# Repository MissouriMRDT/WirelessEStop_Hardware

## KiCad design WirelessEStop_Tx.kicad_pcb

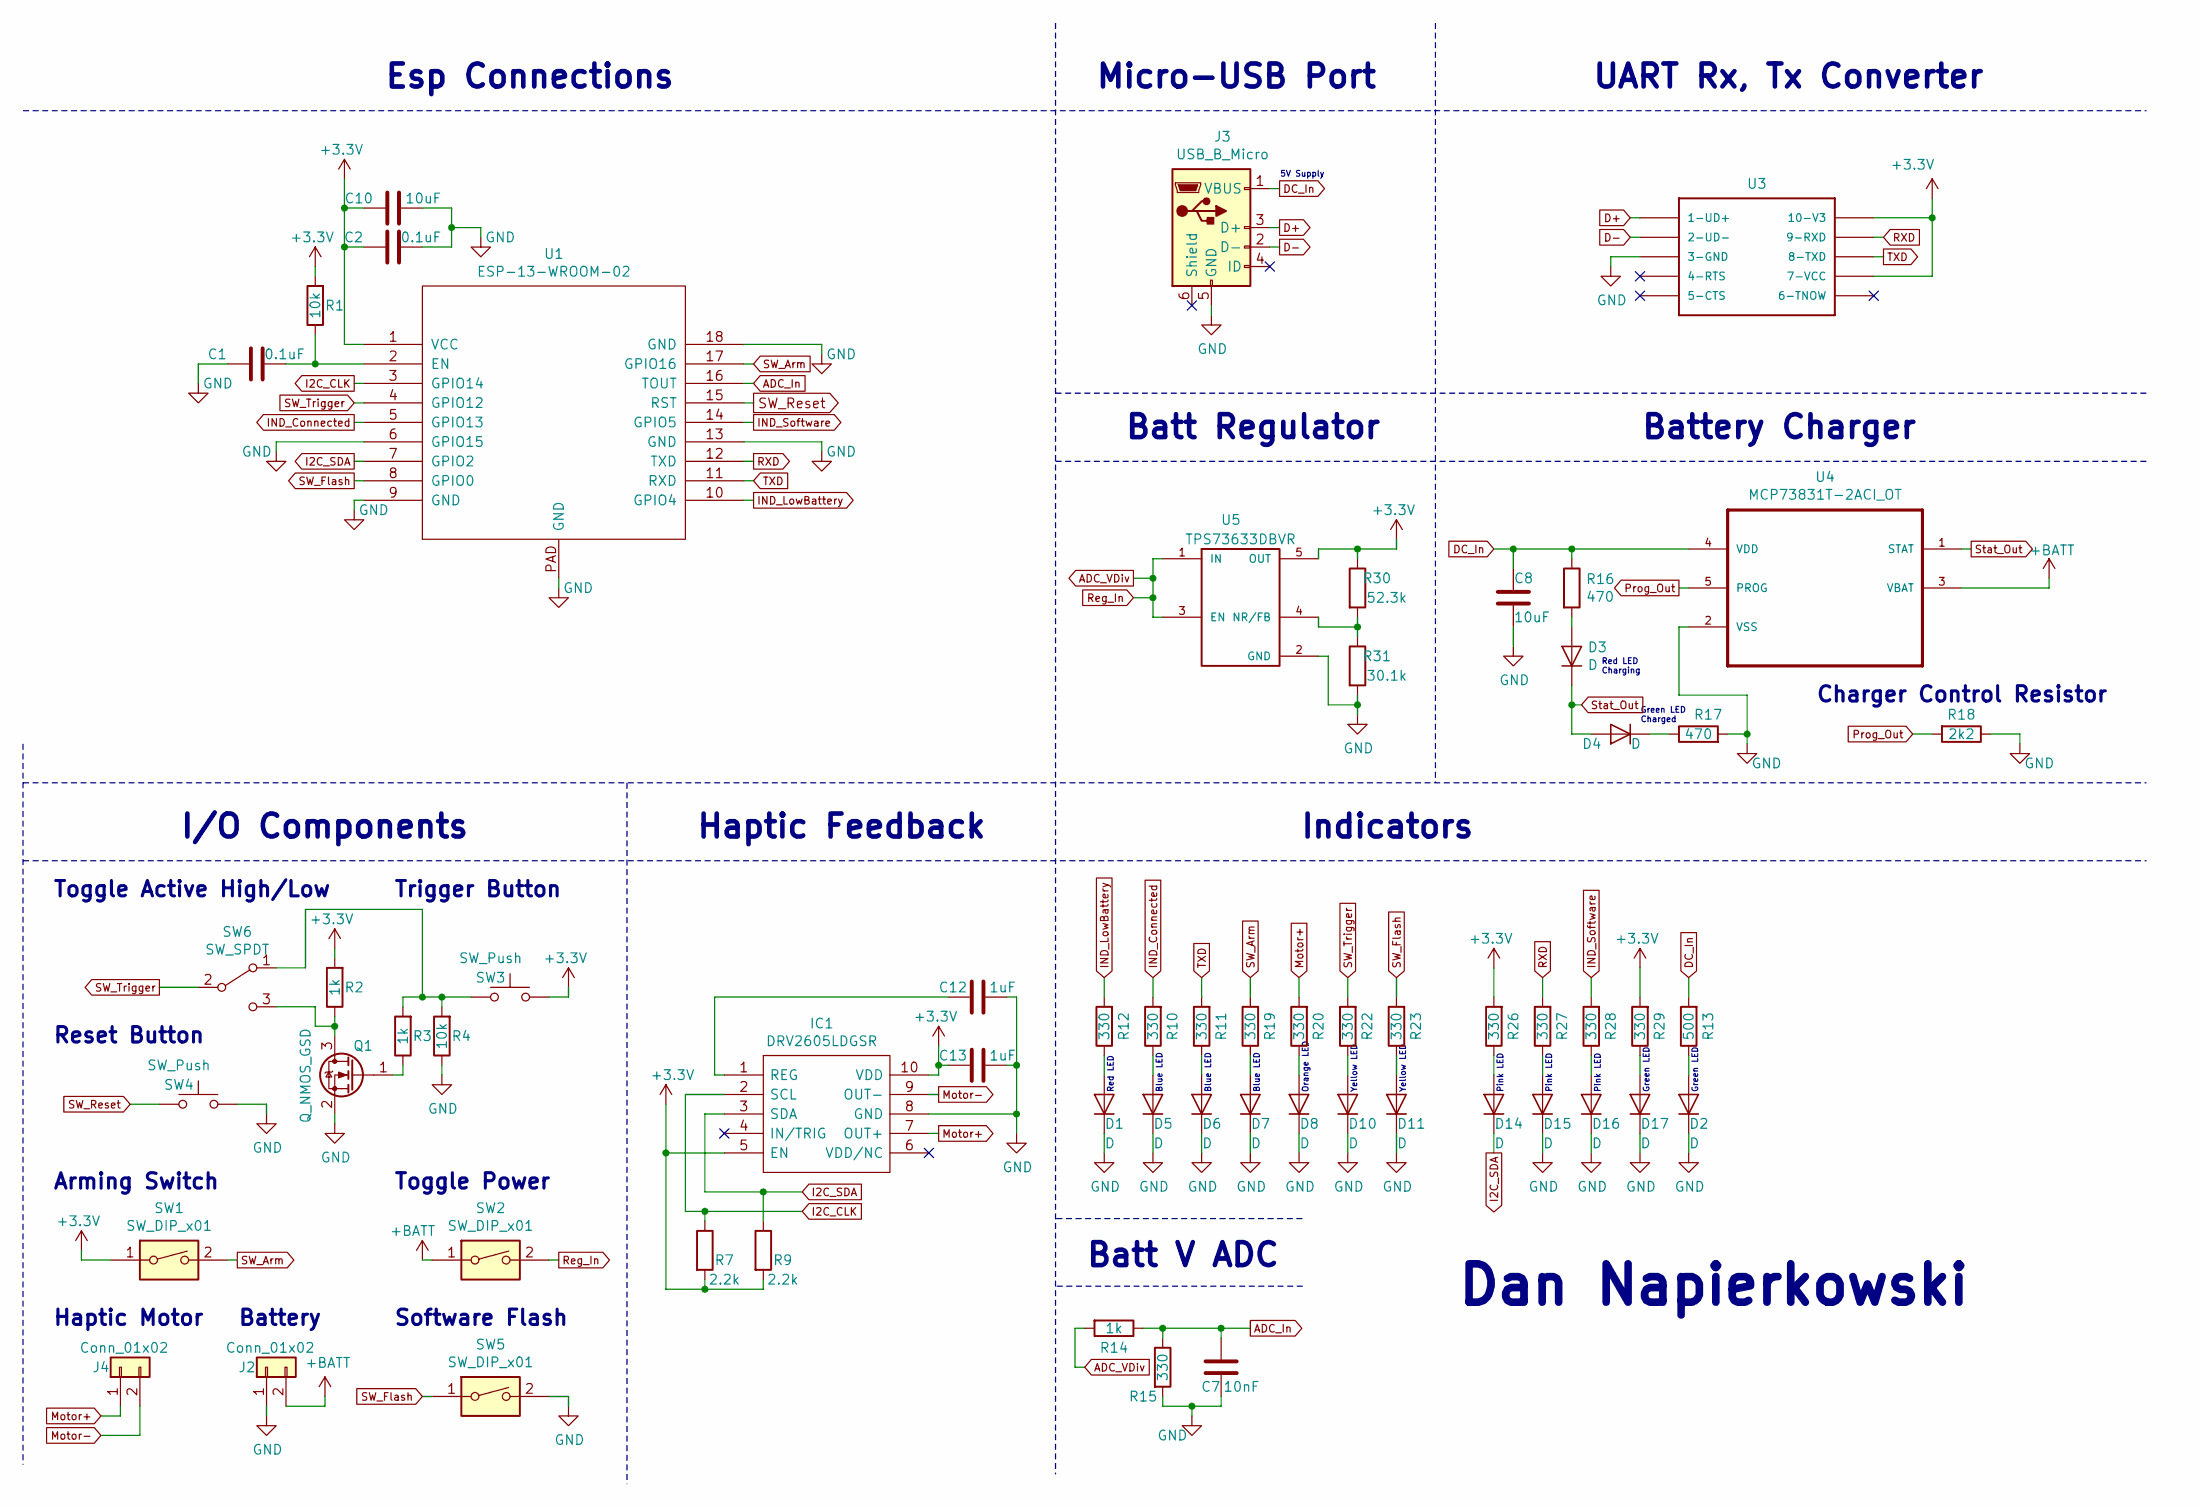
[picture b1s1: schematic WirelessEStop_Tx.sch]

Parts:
C1, C2: 0.1uF; C_0603_1608Metric_Pad1.05x0.95mm_HandSolder
C7: 10nF; C_0603_1608Metric_Pad1.05x0.95mm_HandSolder
C8, C10: 10uF; C_0603_1608Metric_Pad1.05x0.95mm_HandSolder
C12, C13: 1uF; C_0603_1608Metric_Pad1.05x0.95mm_HandSolder
D1, D2, D3, D4, D5, D6, D7, D8, D10, D11, D14, D15, D16, D17: D; LED_0603_1608Metric_Pad1.05x0.95mm_HandSolder
IC1: DRV2605LDGSR; SOP50P490X110-10N; Mouser Part Number 595-DRV2605LDGSR
J2, J4: Conn_01x02; JST_EH_B2B-EH-A_1x02_P2.50mm_Vertical
J3: USB_B_Micro; USB_Micro-B_Amphenol_10103594-0001LF_Horizontal
Q1: Q_NMOS_GSD; SOT95P240X112-3N
R1, R4: 10k; R_0603_1608Metric_Pad1.05x0.95mm_HandSolder
R2, R3, R14: 1k; R_0603_1608Metric_Pad1.05x0.95mm_HandSolder
R7, R9: 2.2k; R_0603_1608Metric_Pad1.05x0.95mm_HandSolder
R10, R11, R12, R15, R19, R20, R22, R23, R26, R27, R28, R29: 330; R_0603_1608Metric_Pad1.05x0.95mm_HandSolder
R13: 500; R_0603_1608Metric_Pad1.05x0.95mm_HandSolder
R16, R17: 470; R_0603_1608Metric_Pad1.05x0.95mm_HandSolder
R18: 2k2; R_0603_1608Metric_Pad1.05x0.95mm_HandSolder
R30: 52.3k; R_0603_1608Metric_Pad1.05x0.95mm_HandSolder
R31: 30.1k; R_0603_1608Metric_Pad1.05x0.95mm_HandSolder
SW1, SW2: SW_DIP_x01; JST_EH_B2B-EH-A_1x02_P2.50mm_Vertical
SW3: SW_Push; JST_EH_B2B-EH-A_1x02_P2.50mm_Vertical
SW4: SW_Push; SW_SPST_TL3305A
SW5: SW_DIP_x01; SW_SPST_TL3305A
SW6: SW_SPDT; JST_EH_B3B-EH-A_1x03_P2.50mm_Vertical
U1: ESP-13-WROOM-02; MODULE_ESP-WROOM-02U
U3: CH340; MSOP10
U4: MCP73831T-2ACI_OT; SOT95P280X145-5N
U5: TPS73633DBVR; SOT95P280X145-5N

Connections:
+3V3: C2.1, C10.1, C13.1, IC1.5 (EN), IC1.10 (VDD), R1.2, R2.2, R7.2, R9.2, R26.2, R29.2, R30.1, SW1.1, SW3.2, U1.1 (VCC), U3.7 (7-VCC), U3.10 (10-V3), U5.5 (OUT)
+BATT: J2.2, SW2.1, U4.3 (VBAT)
ADC_In: C7.2, R14.1, R15.1, U1.16 (TOUT)
ADC_VDiv: R14.2, SW2.2, U5.1 (IN), U5.3 (EN)
D+: J3.3 (D+), U3.1 (1-UD+)
D-: J3.2 (D-), U3.2 (2-UD-)
DC_In: C8.1, J3.1 (VBUS), R13.2, R16.1, U4.4 (VDD)
I2C_CLK: IC1.2 (SCL), R7.1, U1.3 (GPIO14)
I2C_SDA: D14.1 (K), IC1.3 (SDA), R9.1, U1.7 (GPIO2)
IND_Connected: R10.2, U1.5 (GPIO13)
IND_LowBattery: R12.2, U1.10 (GPIO4)
IND_Software: R28.2, U1.14 (GPIO5)
Motor+: IC1.7 (OUT+), J4.1, R20.2
Motor-: IC1.9 (OUT-), J4.2
unnamed: C1.2, R1.1, U1.2 (EN)
unnamed: C12.1, IC1.1 (REG)
unnamed: D1.2 (A), R12.1
unnamed: D2.2 (A), R13.1
unnamed: D3.2 (A), R16.2
unnamed: D4.1 (K), R17.1
unnamed: D5.2 (A), R10.1
unnamed: D6.2 (A), R11.1
unnamed: D7.2 (A), R19.1
unnamed: D8.2 (A), R20.1
unnamed: D10.2 (A), R22.1
unnamed: D11.2 (A), R23.1
unnamed: D14.2 (A), R26.1
unnamed: D15.2 (A), R27.1
unnamed: D16.2 (A), R28.1
unnamed: D17.2 (A), R29.1
unnamed: Q1.1 (G), R3.1
unnamed: Q1.3 (D), R2.1, SW6.3 (C)
unnamed: R3.2, R4.2, SW3.1, SW6.1 (A)
unnamed: R30.2, R31.1, U5.4 (NR/FB)
Prog_Out: R18.2, U4.5 (PROG)
RXD: R27.2, U1.12 (TXD), U3.9 (9-RXD)
SW_Arm: R19.2, SW1.2, U1.17 (GPIO16)
SW_Flash: R23.2, SW5.1, U1.8 (GPIO0)
SW_Reset: SW4.1, U1.15 (RST)
SW_Trigger: R22.2, SW6.2 (B), U1.4 (GPIO12)
Stat_Out: D3.1 (K), D4.2 (A), U4.1 (STAT)
TXD: R11.2, U1.11 (RXD), U3.8 (8-TXD)

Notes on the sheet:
Esp Connections
Micro-USB Port
Battery Charger
Indicators
Charger Control Resistor
Toggle Active High/Low
Trigger Button
Red LED Charging
Green LED Charged
Reset Button
Batt V ADC
5V Supply
I/O Components
Batt Regulator
Haptic Feedback
Haptic Motor
Software Flash
Battery
Toggle Power
Arming Switch
Yellow LED
Blue LED
Orange LED
Pink LED
Green LED
Red LED
Dan Napierkowski
UART Rx, Tx Converter

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
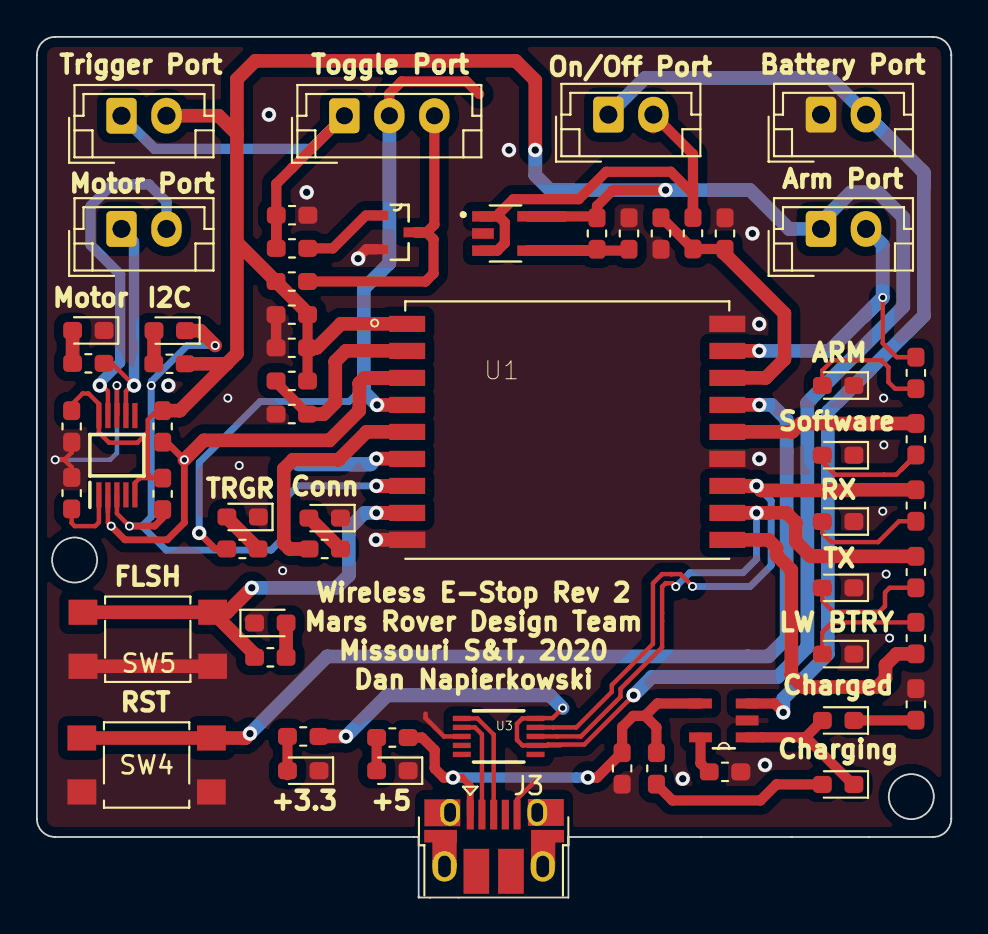
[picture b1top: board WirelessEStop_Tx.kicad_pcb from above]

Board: 2 copper layers, 50.8 x 47.8 mm, 62 parts (1 on the bottom side), 44 nets.

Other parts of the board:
R5: 0; R_0603_1608Metric_Pad1.05x0.95mm_HandSolder

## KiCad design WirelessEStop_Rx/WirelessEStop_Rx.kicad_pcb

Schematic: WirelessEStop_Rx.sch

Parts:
C1, C2: 10u; C_0603_1608Metric_Pad1.05x0.95mm_HandSolder
Conn1: E-Stop_to_BMS; MOLEX_SL_02_Horizontal_NoHole
Conn2: 9V Battery; MOLEX_SL_02_Horizontal_NoHole
D1, D2, D3: LED; LED_0603_1608Metric_Pad1.05x0.95mm_HandSolder
PWR_SW1: SW_Push_SPDT; SW_CuK_OS102011MA1QN1_SPDT_Angled
Q1: 2N7002; SOT-23
R1, R2, R3: 500; R_0603_1608Metric_Pad1.05x0.95mm_HandSolder
U1: OKI; OKI_Horizontal
U2: ESP_8266_01; ESP8266-01

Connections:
+3V3: C2.1, D3.2, U1.3, U2.8
GND: C1.2, C2.2, Conn2.1, R1.2, R2.2, R3.2, U1.2, U2.1
unnamed 2: C1.1, U1.1; also elsewhere on the board
unnamed: Conn1.1, Q1.3 (D)
unnamed: Conn1.2, Q1.2 (S)
unnamed 5: Conn2.2; also elsewhere on the board
unnamed: D1.1, R1.1
unnamed: D1.2, Q1.1 (G), U2.5
unnamed: D2.1, R2.1
unnamed: D2.2, U2.3
unnamed: D3.1, R3.1

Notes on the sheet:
Blue
Red
Green
POWER INPUT
ESP-01 & E-Stop Circuit

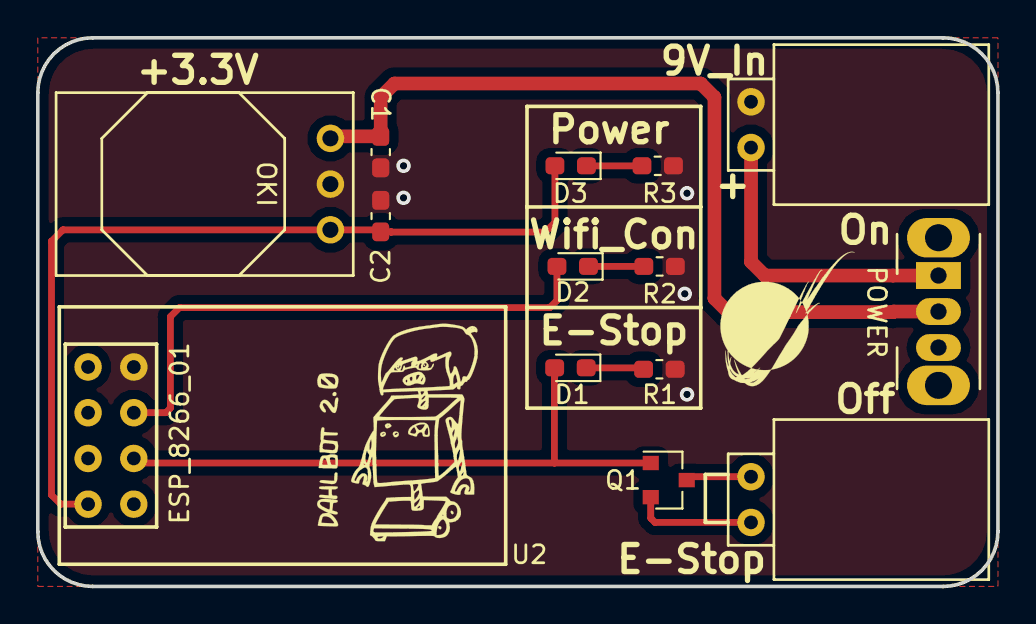
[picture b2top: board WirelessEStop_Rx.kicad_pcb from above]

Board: 2 copper layers, 53.3 x 30.5 mm, 14 parts (0 on the bottom side), 11 nets.

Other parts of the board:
POWER: SW_Push_SPDT; SW_CuK_OS102011MA1QN1_SPDT_Angled

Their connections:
unnamed 2: POWER.2; also elsewhere on the board
unnamed 5: POWER.1; also elsewhere on the board

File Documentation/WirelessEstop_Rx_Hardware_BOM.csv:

Id,Designator,Package,Designation,,Item Name,Part Number,,,Vendor,Quantity,Cost Per Item,,Cost,URL,Comments
,PWR_SW1,SW_CuK_OS102011MA1QN1_SPDT_Angled,Power Switch,,SWITCH SLIDE SPDT 100MA 12V ,CKN9565-ND,,,Digikey,1,"$0.45 for 1, $4.38 for 10",,,https://www.digikey.com/product-detail/en/c-k/OS102011MS2QN1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,
,"C1,C2",C_0603_1608Metric_Pad1.05x0.95mm_HandSolder,10u,,Capacitor,1276-1119-1-ND,,,Digikey,2,"$0.18 for 1, $1.32 for 10",,,https://www.digikey.com/product-detail/en/samsung-electro-me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,
,D1,LED_0603_1608Metric_Pad1.05x0.95mm_HandSolder,LED,,LED RED CLEAR CHIP SMD,160-1447-1-ND,,,Digikey,1,"$0.29 for 1, $2.15 for 10",,,https://www.digikey.com/product-detail/en/lite-on-inc/LTST-C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,
,D2,LED_0603_1608Metric_Pad1.05x0.95mm_HandSolder,LED,,LED BLUE CLEAR CHIP SMD,160-1647-1-ND,,,Digikey,1,"$0.53 for 1, $3.84 for 10",,,https://www.digikey.com/product-detail/en/lite-on-inc/LTST-C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,
,D3,LED_0603_1608Metric_Pad1.05x0.95mm_HandSolder,LED,,LED GREEN CLEAR CHIP SMD,160-1446-1-ND,,,Digikey,1,"$0.29 for 1, $2.15 for 10",,,https://www.digikey.com/product-detail/en/lite-on-inc/LTST-C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,
,Q1,SOT-23,2N7002,,MOSFET N-CH 60V 115MA SOT-23 ,2N7002NCT-ND,,,Digikey,1,"$0.39 for 1, $3.61 for 10",,,https://www.digikey.com/product-detail/en/on-semiconductor/2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,
,"R1,R2,R3",R_0603_1608Metric_Pad1.05x0.95mm_HandSolder,500,,Resistor,RHM510DCT-ND,,,Digikey,3,"$0.10 for 1, $0.87 for 10",,,https://www.digikey.com/product-detail/en/rohm-semiconductor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,
,U1,OKI_Horizontal,OKI,,OKI,811-3014-ND,,,Digikey,1,$4.54 for 1,,,https://www.digikey.com/product-detail/en/murata-power-solut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,
,U2,ESP8266-01,ESP_8266_01,,ESP8266-01,1568-1235-ND,,,Digikey,1,$6.95 for 1,,,https://www.digikey.com/product-detail/en/sparkfun-electroni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,
,Conn1,MOLEX_SL_02_Horizontal_NoHole,E-Stop_to_BMS,,Connector,WM4900-ND,,,Digikey,1,$0.71 for 1,,,https://www.digikey.com/products/en?keywords=WM4900-ND,
,Conn2,MOLEX_SL_02_Horizontal_NoHole,9V Battery,,Connector,WM4900-ND,,,Digikey,1,$0.71 for 1,,,https://www.digikey.com/products/en?keywords=WM4900-ND,

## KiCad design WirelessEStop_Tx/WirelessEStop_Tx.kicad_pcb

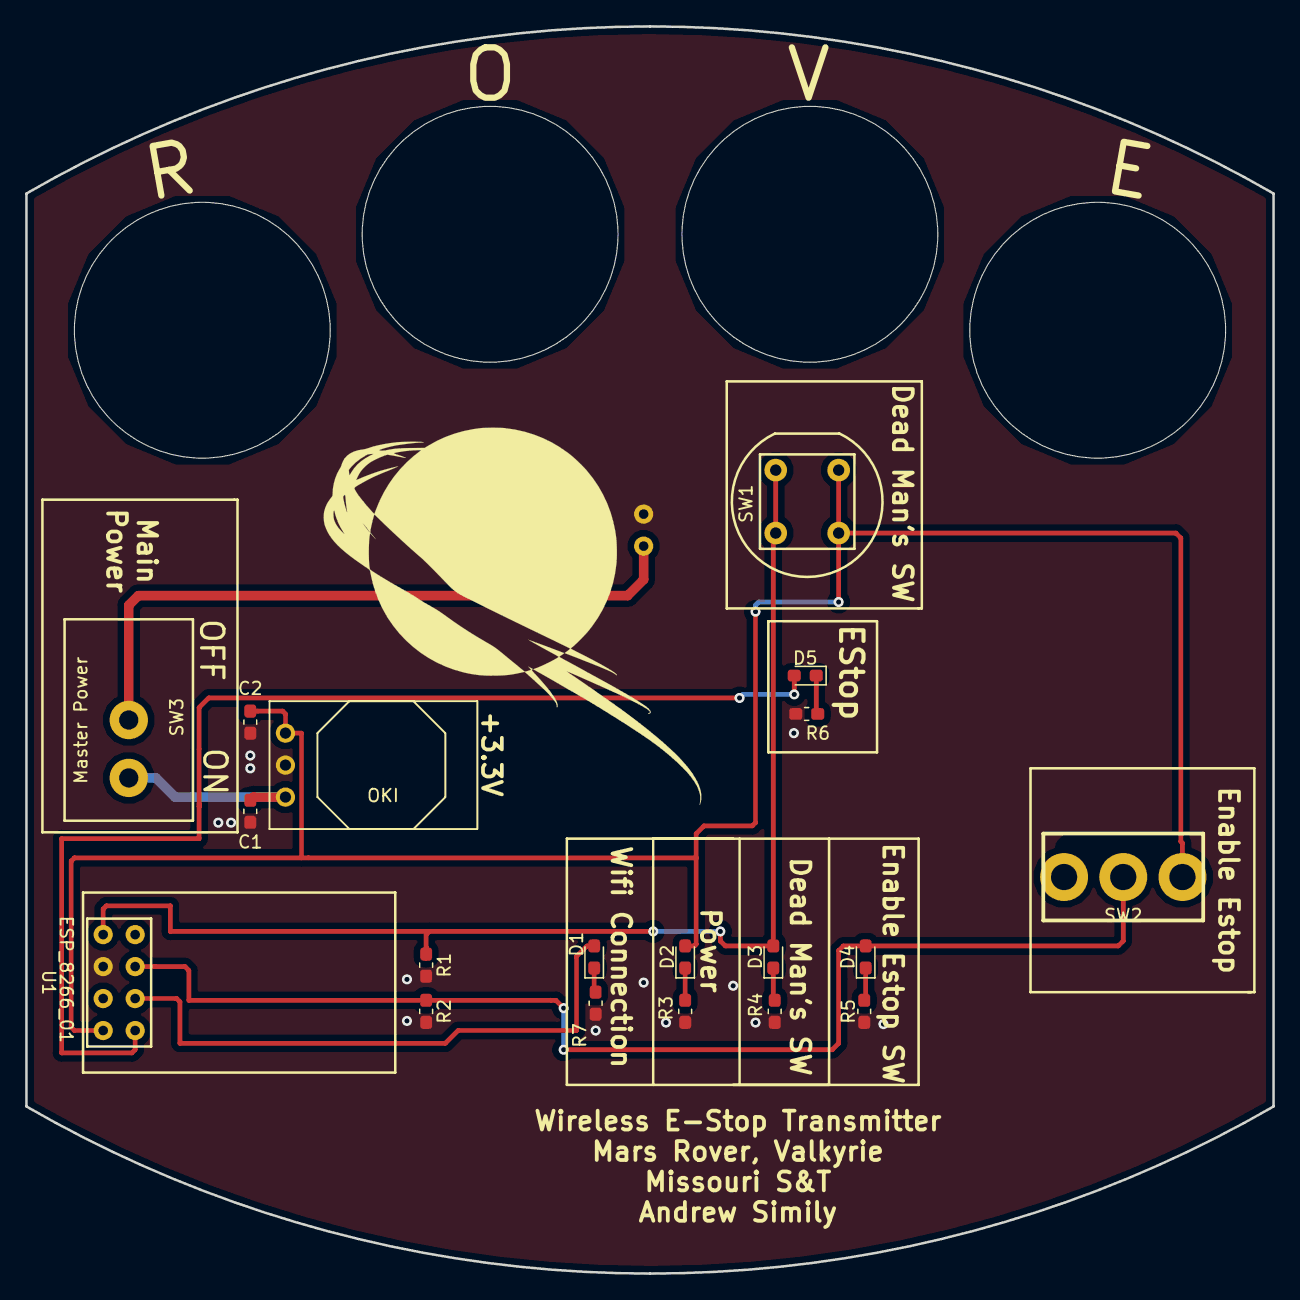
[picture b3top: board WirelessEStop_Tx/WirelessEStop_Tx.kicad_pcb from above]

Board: 2 copper layers, 99.1 x 99.1 mm, 20 parts (1 on the bottom side), 13 nets.

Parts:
C1, C2: 10u; C_0603_1608Metric_Pad1.05x0.95mm_HandSolder
Conn1: 9V Batt; MOLEX_SL_02_Horizontal_NoHole
D1, D2, D3, D4, D5: LED; LED_0603_1608Metric_Pad1.05x0.95mm_HandSolder
R1, R2: 10K; R_0603_1608Metric_Pad1.05x0.95mm_HandSolder
R3, R4, R5, R6, R7: 500; R_0603_1608Metric_Pad1.05x0.95mm_HandSolder
SW1: MOM Switch; D6_SPST
SW2: Maintain Switch; ToggleSwitch_SPDT
SW3: Master Power; SlideSwitch_SPST
U1: ESP_8266_01; ESP8266-01
U2: OKI; OKI_Horizontal

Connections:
+3V3: C2.2, D2.2, SW1.1, SW2.3, U1.8, U2.3
/Vin: Conn1.2, SW3.2
GND: C1.1, C2.1, Conn1.1, R1.2, R2.2, R3.2, R4.2, R5.2, R6.2, R7.2, SW2.1, U1.4, U2.2
MOM_IN: D3.2, R1.1, SW1.2, U1.2
Maintain_IN: D4.2, R2.1, SW2.2, U1.3
unnamed: C1.2, SW3.1, U2.1
unnamed: D1.1, R7.1
unnamed: D2.1, R3.1
unnamed: D3.1, R4.1
unnamed: D4.1, R5.1
unnamed: D5.1, R6.1
SW_EStop: D5.2, U1.7
SW_Link_EN: D1.2, U1.5

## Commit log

2018-11-13 Corrected Github File Structure
2018-11-13 Fixed files and stuff
    Organized some files and also worked on the footprint assignments and started to create a footprint for one of the three switches.
2018-11-29 Worked on the footprints
    Finished the footprints for the switches. Still need to be checked for accuracy.
2018-11-29 More footprint updates
    Made a footprint for the ESP8266-01, but it still needs to be checked.
2018-11-30 Board Review
    Nothing much at the moment, but a lot needs to be changed.
2018-11-30 1st Board Review Changes
    Made a little bit of progress on some of the changes that needed to be made after the board review.
2018-12-01 Created Board Outline
2018-12-10 Finished up the Transmitter Schematic
    Just more work done
2018-12-10 Revert "Finished up the Transmitter Schematic"
    This reverts commit 0529c396fdec7017beb922822e4a7a479dabca41.
2018-12-14 Worked on Board Layout
    Pretty much finished the board. Need the BOM and stuff yet.
2018-12-14 Worked on the BOM
    Should be finished, but I'm not certain
2018-12-19 Updated Schematic
    Changed AP1509 back to an OKI
2018-12-19 Fixed Board
    Changed AP1509 and fixed the ESP8266-01
2018-12-19 Updated BOM
    Fixed the items on the BOM
2018-12-19 Created Gerbs
2018-12-19 Fixed Gerbs?
2019-03-01 Fixed Errors and made neater
2019-03-02 Made the Reciever Schematic
2019-03-02 Board Layout mostly complete
2019-03-02 Tiny update
2019-03-02 Went over a few things
2019-03-04 Something small in schematic
2019-03-05 Adjusted things & made Gerbs
2019-03-07 Started BOM
2019-03-07 Tentative BOM completed
2019-12-05 This bout to be some dope shiz
2019-12-08 What the fuck did you just fucking say about me, you little bitch? I'll have you know I graduated top of my class in the Navy Seals, and I've been involved in numerous secret raids on Al-Quaeda, and 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
2019-12-09 Bee Movie Script - Dialogue Transcript According to all known laws of aviation, there is no way a bee should be able to fly. Its wings are too small to get its fat little body off the ground. The bee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
2019-12-11 if(reader == "Eli") print("Get Fucked")
2019-12-11 Schematic is done, nothing snarky to say other than I'm the fuckin best
2019-12-11 commit kiddos
2019-12-12 If you can read this message, please, you need to do something. I'm locked in the github server room, and the things I've seen.... Oh fuck, I think I hear a comp sci coming OH GOD PLEASE NO, HEL......
2019-12-13 big pp
2019-12-14 Eli suck my dick
2019-12-14 The only thing longer than my commit names are... MY LOVE OF JESUS CHRIST CAN I GET AN AMEN?
2019-12-14 Bout to be date time with the ESP (Extra special person)
2019-12-14 Please let the sweet release of death take me soon
2019-12-19 Rethinkimg things
2020-01-07 Whats the difference between Dahlbot, and a baby? I dont want to strangle Dahlbot to death
2020-01-07 IDK dude, just think of a clever joke and give me credit for it. I just want to play dota
2020-01-07 I ate myself anf was dissapointed
2020-01-07 Zak your name is weird since its only 3 letters, but its also as many letters as needed. Its a weird juxtaposition of right and wrong and it makes me uncomfortable
2020-01-07 Three projects up, three projects up. Suck my dick dumb shits
2020-01-21 Created Step File
2020-02-04 rev 2 work yay
2020-02-06 Finished Rev 2, added silks
2020-02-06 Yeet Yeet
2020-02-06 Whoop Whoop, Zoop Zoop
2020-02-07 Added Documentation
2020-02-26 Added Gerbs
2020-03-26 zipped gerbs
